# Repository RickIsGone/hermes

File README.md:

# Bike active aero handler
this project is made for the **Hermes YSWS**  
*Bike active aero handler* is a PCB which gets power from the bike's battery and based on the lean of the bike, which is obtained with the *BMI160* gyroscope controlls the active winglets moved by the 6 servomotors connected via the PWM pins 

## The PCB

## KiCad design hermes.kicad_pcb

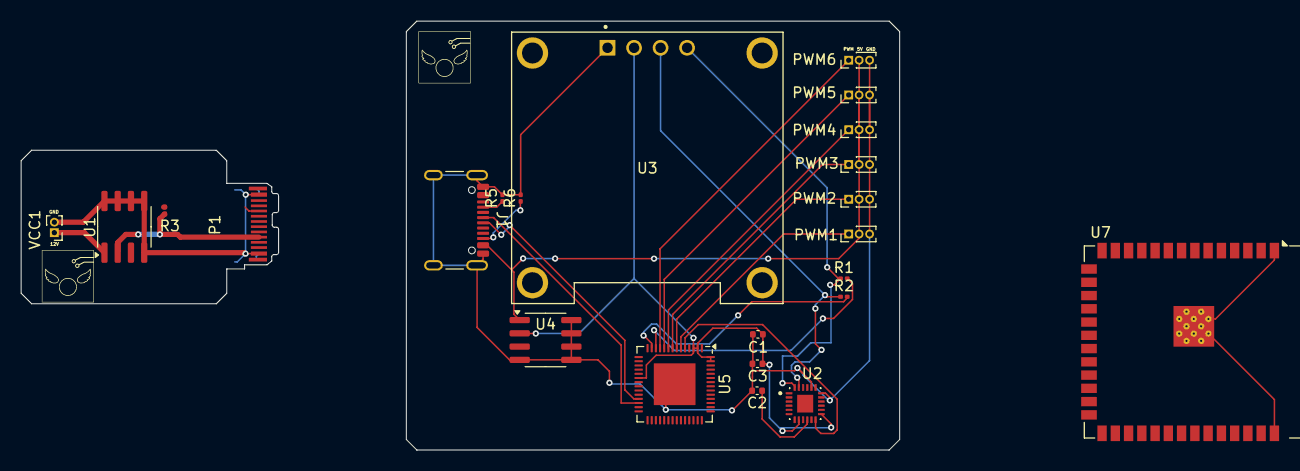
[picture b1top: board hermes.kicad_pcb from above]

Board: 2 copper layers, 84.2 x 41.1 mm, 23 parts (0 on the bottom side), 23 nets.

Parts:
C1, C2, C3: C; C_0402_1005Metric
J1: USB_C_Receptacle_USB2.0_16P; USB_C_Receptacle_GCT_USB4105-xx-A_16P_TopMnt_Horizontal
P1: USB_C_Plug_USB2.0; USB_C_Plug_JAE_DX07P024AJ1
PWM1, PWM2, PWM3, PWM4, PWM5, PWM6: Conn_01x03_MountingPin; PinHeader_1x03_P1.00mm_Vertical
R1, R2: 4.7K; R_0201_0603Metric
R3, R5, R6: 5.1K; R_0201_0603Metric
U1: XL1509-5.0; SOIC-8_3.9x4.9mm_P1.27mm
U2: MPU-6500; QFN40P300X300X95-25N
U3: DM-OLED096-636; MODULE_DM-OLED096-636
U4: XL1509-3.3; SOIC-8_3.9x4.9mm_P1.27mm
U5: ESP32-S3; QFN-56-1EP_7x7mm_P0.4mm_EP4x4mm
U7: ESP32-S3-WROOM-1
VCC1: Conn_01x02_MountingPin; PinHeader_1x02_P1.00mm_Vertical

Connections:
3V3: C1.1, C3.2, U2.8 (VDDIO), U2.13 (VDD), U3.2 (VCC_IN), U4.2 (OUT), U5.2 (VDD3P3), U5.3 (VDD3P3), U5.20 (VDD3P3_RTC), U5.29 (VDD_SPI), U5.46 (VDD3P3_CPU), U5.55 (VDDA), U5.56 (VDDA)
5V: J1.A4 (VBUS), J1.A9 (VBUS), J1.B4 (VBUS), J1.B9 (VBUS), PWM1.2, PWM2.2, PWM3.2, PWM4.2, PWM5.2, PWM6.2, U4.1 (VIN)
12V: U1.1 (VIN), VCC1.1
ACCELINT: U2.12 (INT), U5.5 (GPIO0)
GND: C1.2, C2.2, C3.1, J1.A1 (GND), J1.A12 (GND), J1.B1 (GND), J1.B12 (GND), J1.S1 (SHIELD), P1.A1 (GND), P1.A12 (GND), P1.B1 (GND), P1.B12 (GND), P1.S1 (SHIELD), PWM1.3, PWM2.3, PWM3.3, PWM4.3, PWM5.3, PWM6.3, R5.2, R6.2, U1.4 (~EN), U1.5 (GND), U1.6 (GND), U1.7 (GND), U1.8 (GND), U2.18 (GND), U2.20 (RESV_2), U3.1 (GND), U4.4 (~EN), U4.5 (GND), U4.6 (GND), U4.7 (GND), U4.8 (GND), U5.57 (GND), VCC1.2
unnamed: J1.A5 (CC1), R5.1
unnamed: J1.B5 (CC2), R6.1
unnamed: P1.A5 (CC), R3.1
unnamed: C2.1, U2.10 (REGOUT)
unnamed: R1.2, U5.12 (GPIO7)
unnamed: R2.2, U5.13 (GPIO8)
unnamed: U7.1 (GND), U7.40 (GND), U7.41 (GND)
PWM1: PWM1.1, U5.6 (GPIO1)
PWM2: PWM2.1, U5.7 (GPIO2)
PWM3: PWM3.1, U5.8 (GPIO3)
PWM4: PWM4.1, U5.9 (GPIO4)
PWM5: PWM5.1, U5.10 (GPIO5)
PWM6: PWM6.1, U5.11 (GPIO6)
SCL: R2.1, U2.23 (SCL/SCLK), U3.3 (SCL)
SDA: R1.1, U2.24 (SDA/SDI), U3.4 (SDA)
USB_D+: J1.A6 (D+), U5.26 (GPIO20/USB_D+)
USB_D-: J1.A7 (D-), U5.25 (GPIO19/USB_D-)
VBUS: P1.A4 (VBUS), P1.A9 (VBUS), P1.B4 (VBUS), P1.B9 (VBUS), R3.2, U1.2 (OUT)

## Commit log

2025-07-28 init repo
2025-07-28 added gbr files
2025-07-29 old update, now working on new board
2025-07-30 new pcb and code
2025-07-30 made project compile
